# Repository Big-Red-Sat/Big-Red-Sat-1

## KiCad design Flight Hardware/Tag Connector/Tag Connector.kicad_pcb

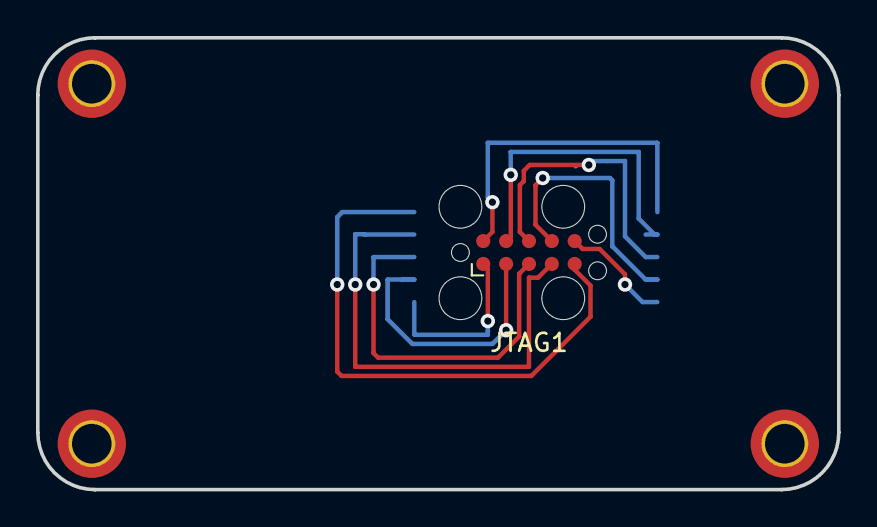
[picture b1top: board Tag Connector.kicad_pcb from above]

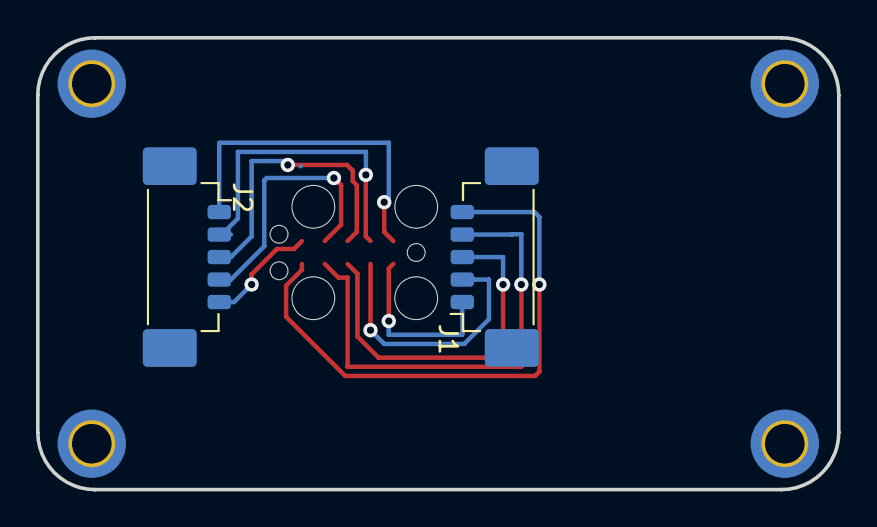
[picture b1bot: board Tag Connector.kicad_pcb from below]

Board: 2 copper layers, 44.5 x 25.1 mm, 3 parts (2 on the bottom side), 10 nets.

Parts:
J1, J2: Conn_01x05_Male; Molex_PicoBlade_53398-0571_1x05-1MP_P1.25mm_Vertical
JTAG1: Conn_02x05_Odd_Even; Tag-Connect_TC2050-IDC-FP_2x05_P1.27mm_Vertical

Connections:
+3V3: J1.1, JTAG1.1
GND: J2.5, JTAG1.6
unnamed: J2.1, JTAG1.10
unnamed: J2.2, JTAG1.9
unnamed: J2.3, JTAG1.8
Rx: J1.5, JTAG1.5
TCK: J1.4, JTAG1.4
TDO-TDI: J1.2, JTAG1.2
TESTVPP: J1.3, JTAG1.3
Tx: J2.4, JTAG1.7

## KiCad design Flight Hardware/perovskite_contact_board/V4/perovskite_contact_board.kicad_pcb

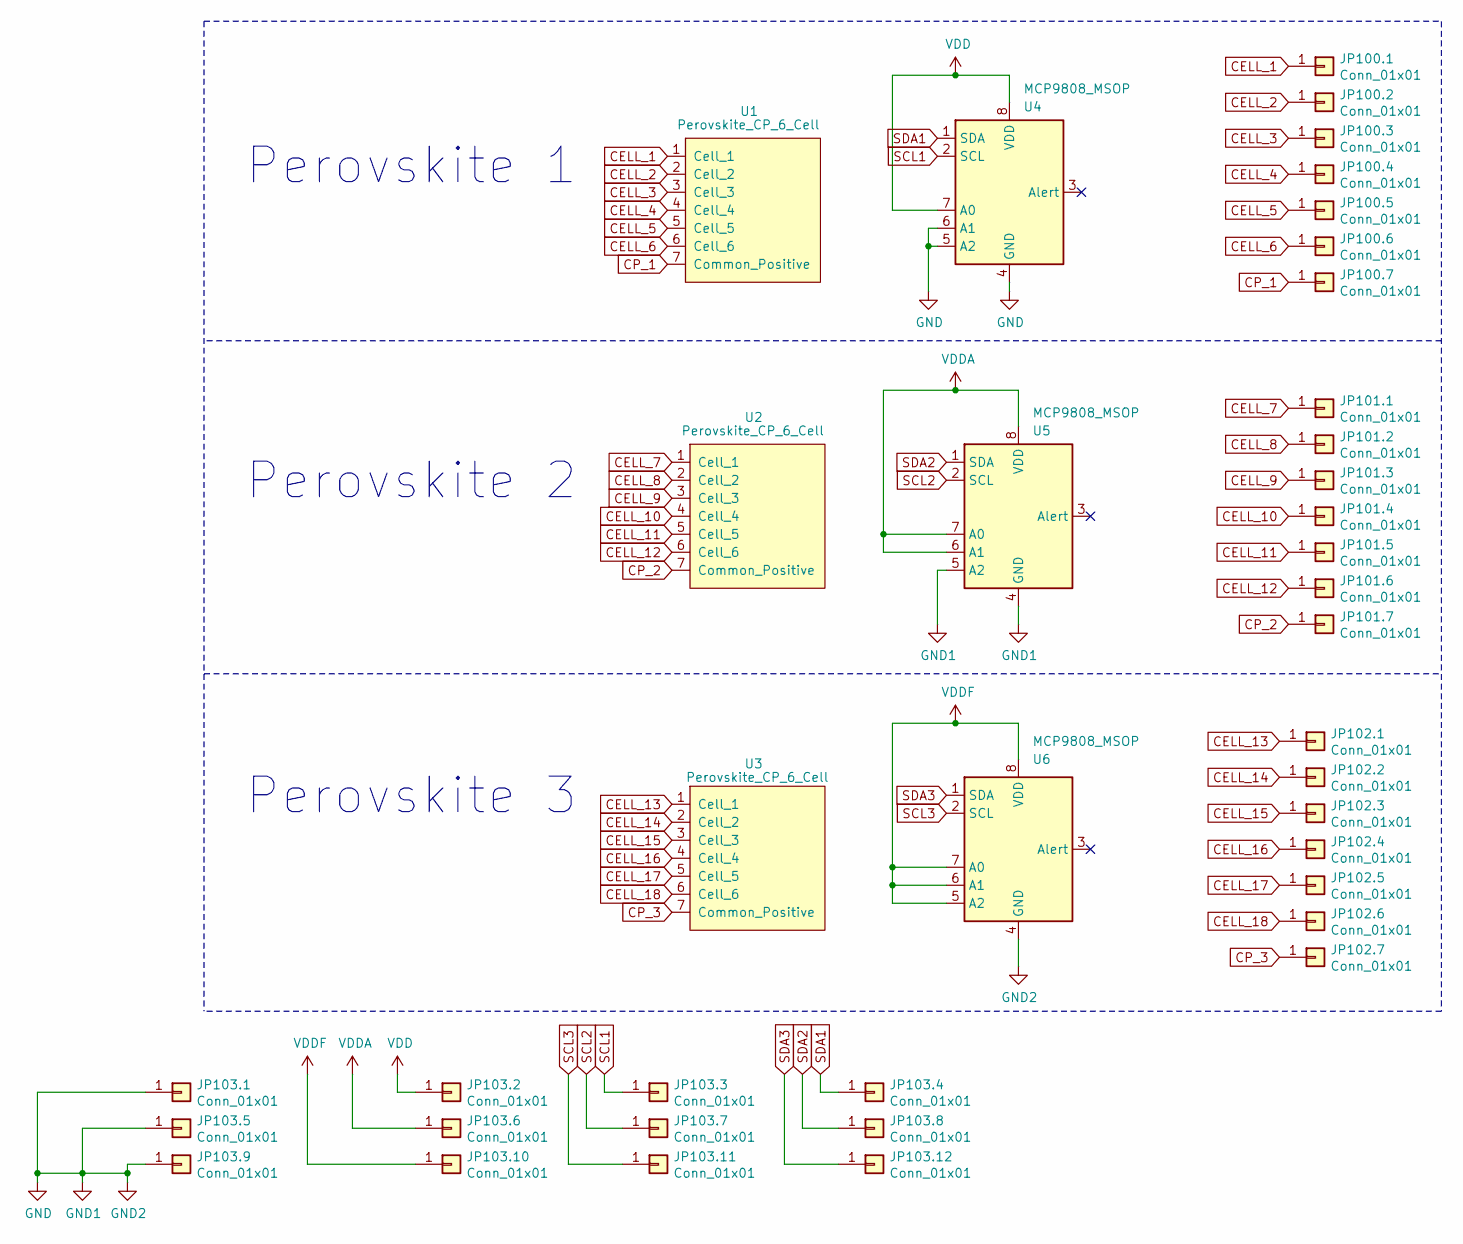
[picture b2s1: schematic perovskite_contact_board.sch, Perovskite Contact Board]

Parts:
JP100.1, JP100.2, JP100.3, JP100.4, JP100.5, JP100.6, JP100.7, JP101.1, JP101.2, JP101.3, JP101.4, JP101.5, JP101.6, JP101.7, JP102.1, JP102.2, JP102.3, JP102.4, JP102.5, JP102.6, JP102.7, JP103.1, JP103.2, JP103.3, JP103.4, JP103.5, JP103.6, JP103.7, JP103.8, JP103.9, JP103.10, JP103.11, JP103.12: Conn_01x01; TestPoint_Pad_D2.0mm
U1, U2, U3: Perovskite_CP_6_Cell; Perovskite
U4, U5, U6: MCP9808_MSOP; MCP9804_With_Hole

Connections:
CELL_1: JP100.1.1, U1.1 (Cell_1)
CELL_2: JP100.2.1, U1.2 (Cell_2)
CELL_3: JP100.3.1, U1.3 (Cell_3)
CELL_4: JP100.4.1, U1.4 (Cell_4)
CELL_5: JP100.5.1, U1.5 (Cell_5)
CELL_6: JP100.6.1, U1.6 (Cell_6)
CELL_7: JP101.1.1, U2.1 (Cell_1)
CELL_8: JP101.2.1, U2.2 (Cell_2)
CELL_9: JP101.3.1, U2.3 (Cell_3)
CELL_10: JP101.4.1, U2.4 (Cell_4)
CELL_11: JP101.5.1, U2.5 (Cell_5)
CELL_12: JP101.6.1, U2.6 (Cell_6)
CELL_13: JP102.1.1, U3.1 (Cell_1)
CELL_14: JP102.2.1, U3.2 (Cell_2)
CELL_15: JP102.3.1, U3.3 (Cell_3)
CELL_16: JP102.4.1, U3.4 (Cell_4)
CELL_17: JP102.5.1, U3.5 (Cell_5)
CELL_18: JP102.6.1, U3.6 (Cell_6)
CP_1: JP100.7.1, U1.7 (Common_Positive)
CP_2: JP101.7.1, U2.7 (Common_Positive)
CP_3: JP102.7.1, U3.7 (Common_Positive)
GND: JP103.1.1, JP103.5.1, JP103.9.1, U4.4 (GND), U4.5 (A2), U4.6 (A1), U5.4 (GND), U5.5 (A2), U6.4 (GND); also elsewhere on the board
SCL1: JP103.3.1, U4.2 (SCL)
SCL2: JP103.7.1, U5.2 (SCL)
SCL3: JP103.11.1, U6.2 (SCL); also elsewhere on the board
SDA1: JP103.4.1, U4.1 (SDA)
SDA2: JP103.8.1, U5.1 (SDA); also elsewhere on the board
SDA3: JP103.12.1, U6.1 (SDA)
VDD: JP103.2.1, U4.7 (A0), U4.8 (VDD); also elsewhere on the board
VDDA: JP103.6.1, U5.6 (A1), U5.7 (A0), U5.8 (VDD); also elsewhere on the board
VDDF: JP103.10.1, U6.5 (A2), U6.6 (A1), U6.7 (A0), U6.8 (VDD); also elsewhere on the board

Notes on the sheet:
Perovskite 1
Perovskite 2
Perovskite 3

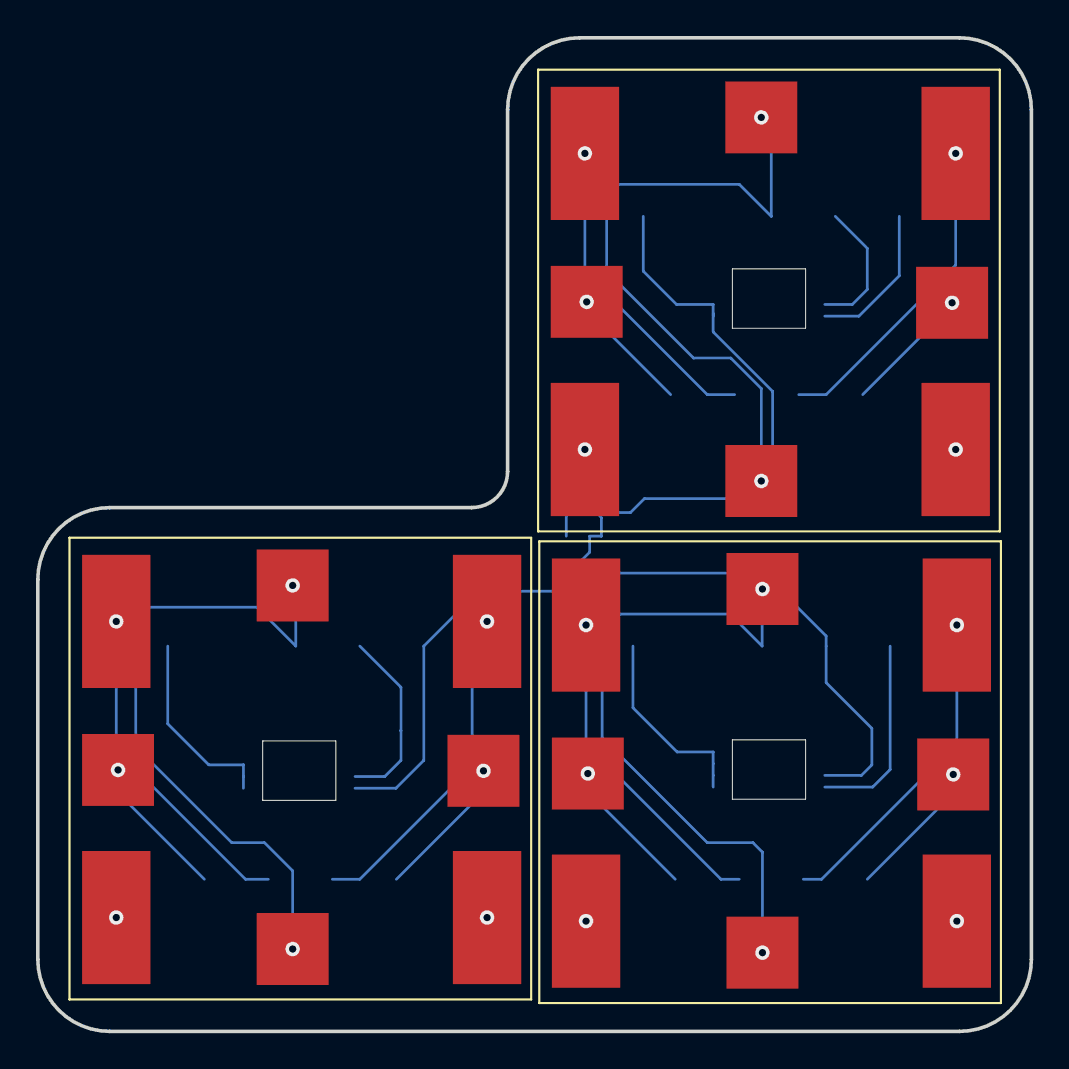
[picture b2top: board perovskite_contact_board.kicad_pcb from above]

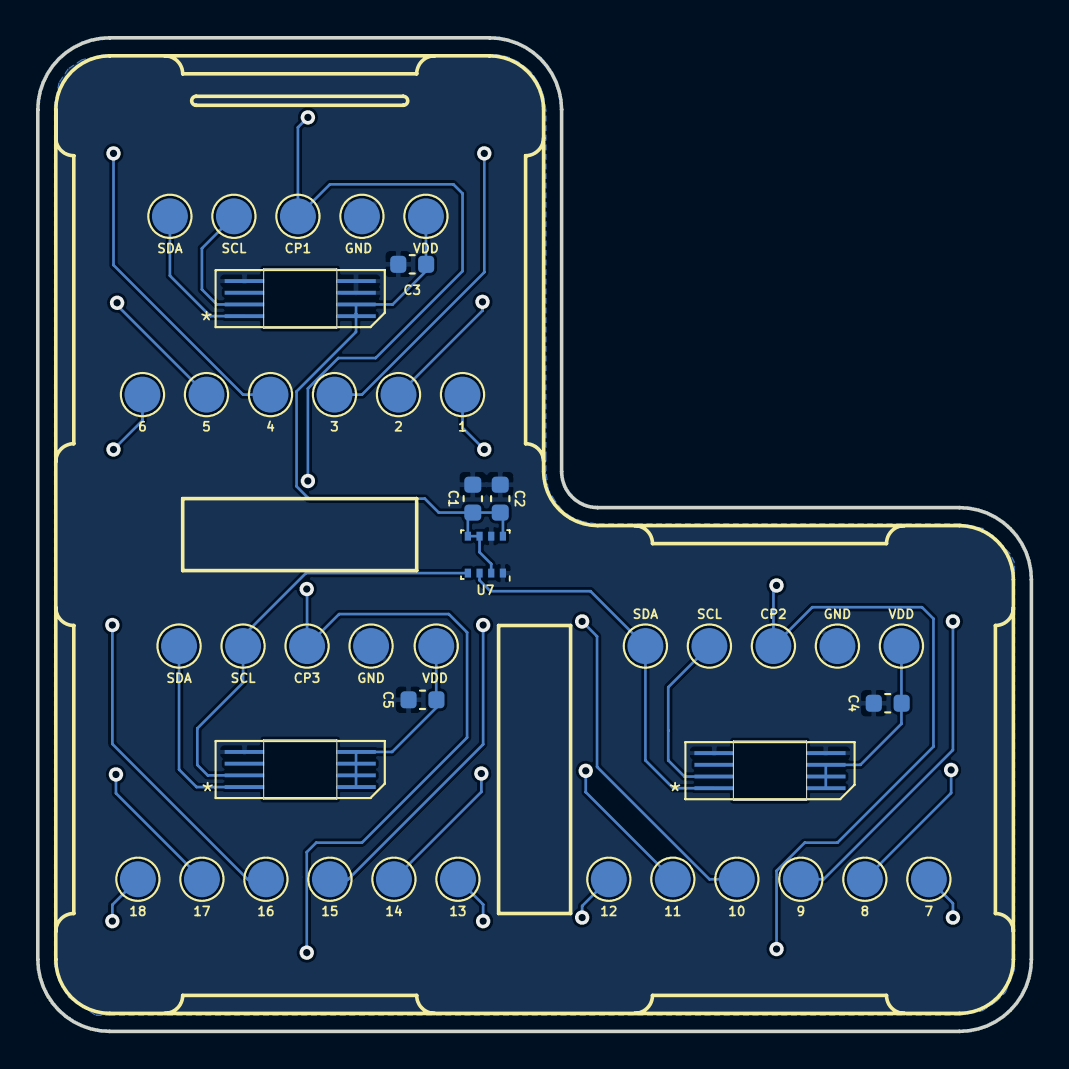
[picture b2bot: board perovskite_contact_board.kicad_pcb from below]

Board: 2 copper layers, 55.2 x 55.2 mm, 45 parts (42 on the bottom side), 31 nets.

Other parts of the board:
C1, C2, C3, C4, C5: 0.1u; C_0603_1608Metric
U7: BME280; Bosch_LGA-8_2.5x2.5mm_P0.65mm_ClockwisePinNumbering

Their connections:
GND: C1.2, C2.2, C3.2, C4.2, C5.2, U7.1, U7.7; also elsewhere on the board
SCL3: U7.4; also elsewhere on the board
SDA2: U7.3; also elsewhere on the board
VDD: C1.1, C2.1, C3.1, U7.2, U7.5, U7.6, U7.8; also elsewhere on the board
VDDA: C4.1; also elsewhere on the board
VDDF: C5.1; also elsewhere on the board

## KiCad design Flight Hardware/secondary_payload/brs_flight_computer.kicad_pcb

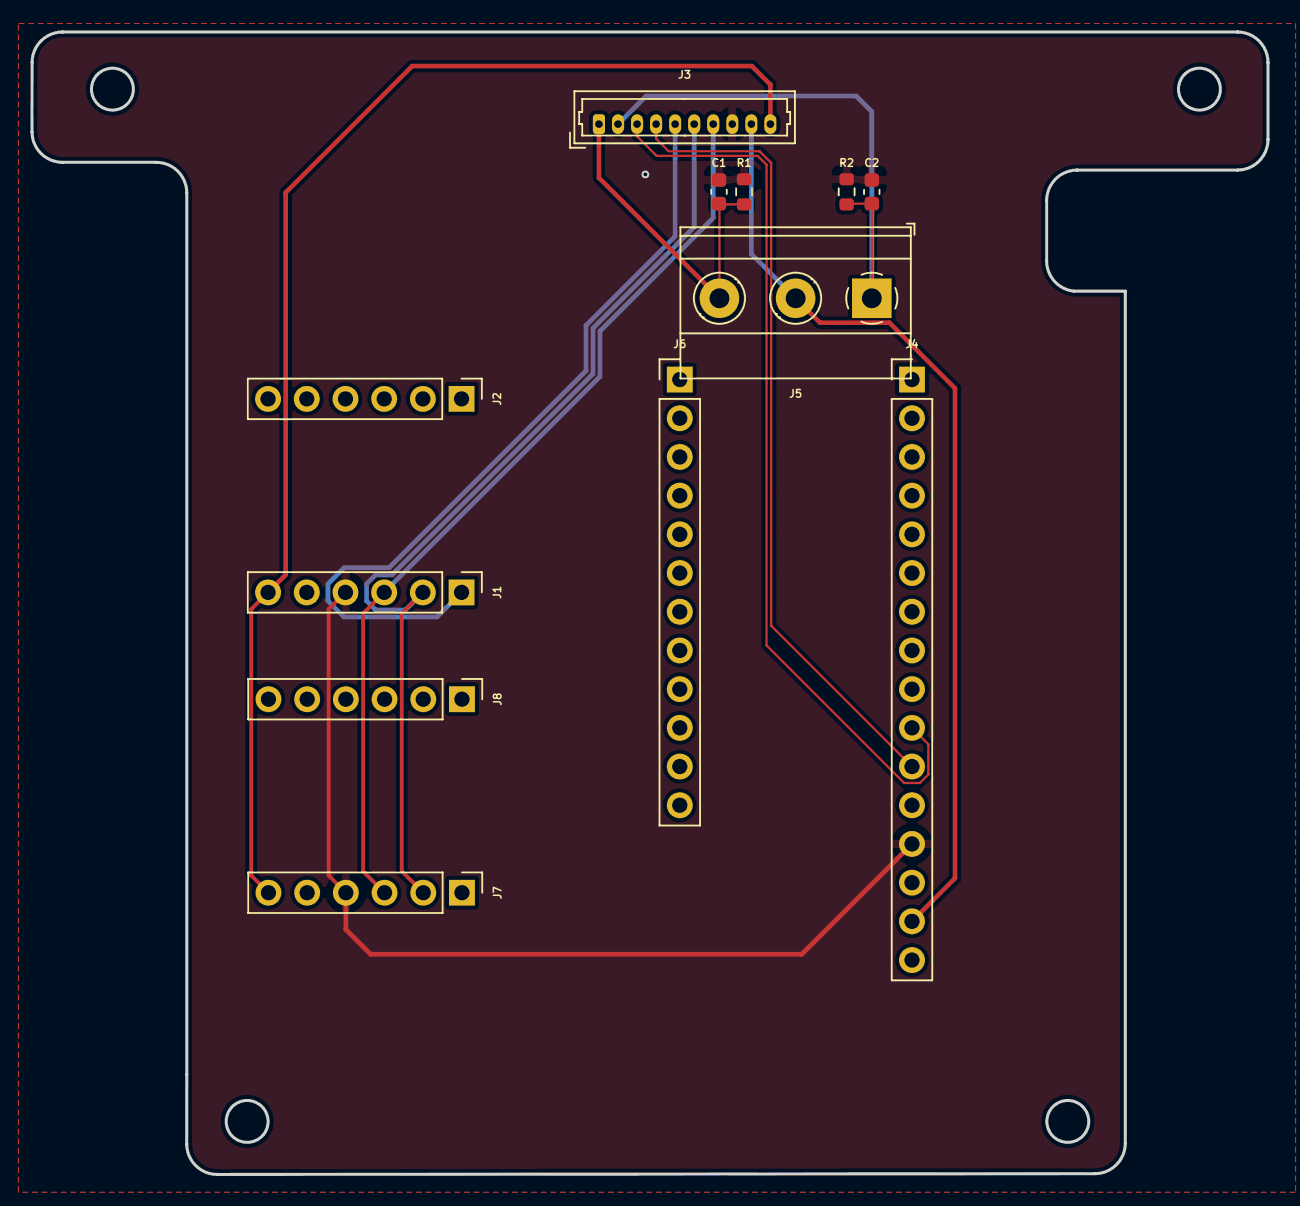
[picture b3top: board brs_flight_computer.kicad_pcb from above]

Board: 2 copper layers, 81.1 x 75.0 mm, 12 parts (0 on the bottom side), 10 nets.

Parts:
C1, C2: C; C_0603_1608Metric
J1, J2, J7, J8: Conn_01x06_Male; PinHeader_1x06_P2.54mm_Vertical
J3: Conn_01x10_Male; Molex_PicoBlade_53047-1010_1x10_P1.25mm_Vertical
J4: Conn_01x16_Male; PinHeader_1x16_P2.54mm_Vertical
J5: Conn_01x03_Male; TerminalBlock_Phoenix_MKDS-1,5-3_1x03_P5.00mm_Horizontal
J6: Conn_01x12_Male; PinHeader_1x12_P2.54mm_Vertical
R1, R2: R; R_0603_1608Metric

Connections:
/MAG_INT: J1.1, J3.5
/NC_V: C1.1, J3.1, J5.3, R1.1
/NO_V: C2.1, J3.2, J5.1, R2.1
/SCL: J1.3, J3.7, J7.3
/SDA: J1.2, J3.6, J7.2
/SET: J3.4, J4.11
/UNSET: J3.3, J4.10
GND: C1.2, C2.2, J1.4, J3.8, J4.13, J7.4, R1.2, R2.2
VDDF: J1.6, J3.10, J7.6
VPP: J3.9, J4.15, J5.2

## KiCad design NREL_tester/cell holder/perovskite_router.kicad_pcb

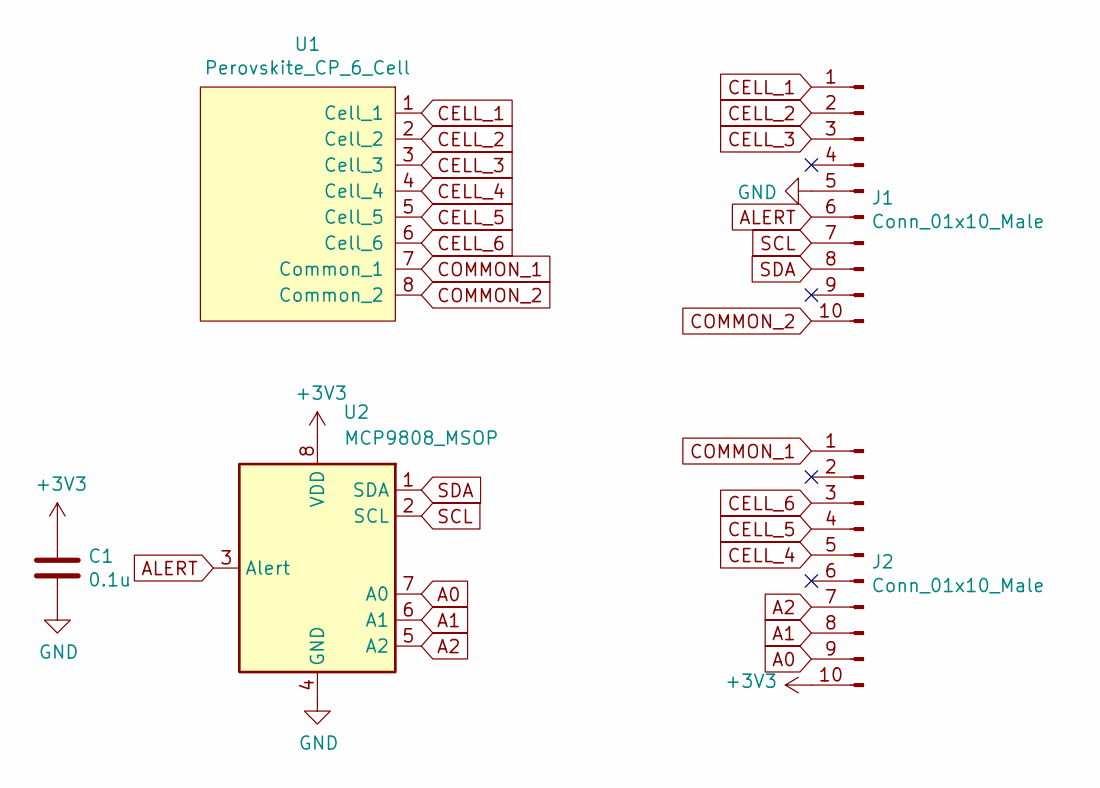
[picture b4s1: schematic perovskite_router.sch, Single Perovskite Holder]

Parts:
C1: 0.1u; C_0603_1608Metric_Pad1.08x0.95mm_HandSolder
J1, J2: Conn_01x10_Male; PinHeader_1x10_P2.54mm_Vertical
U1: Perovskite_CP_6_Cell; Perovskite
U2: MCP9808_MSOP; MCP9804_With_Hole

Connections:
+3V3: C1.1, J2.10, U2.8 (VDD)
A0: J2.9, U2.7 (A0)
A1: J2.8, U2.6 (A1)
A2: J2.7, U2.5 (A2)
ALERT: J1.6, U2.3 (Alert)
CELL_1: J1.1, U1.1 (Cell_1)
CELL_2: J1.2, U1.2 (Cell_2)
CELL_3: J1.3, U1.3 (Cell_3)
CELL_4: J2.5, U1.4 (Cell_4)
CELL_5: J2.4, U1.5 (Cell_5)
CELL_6: J2.3, U1.6 (Cell_6)
COMMON_1: J2.1, U1.7 (Common_1)
COMMON_2: J1.10, U1.8 (Common_2)
GND: C1.2, J1.5, U2.4 (GND)
SCL: J1.7, U2.2 (SCL)
SDA: J1.8, U2.1 (SDA)

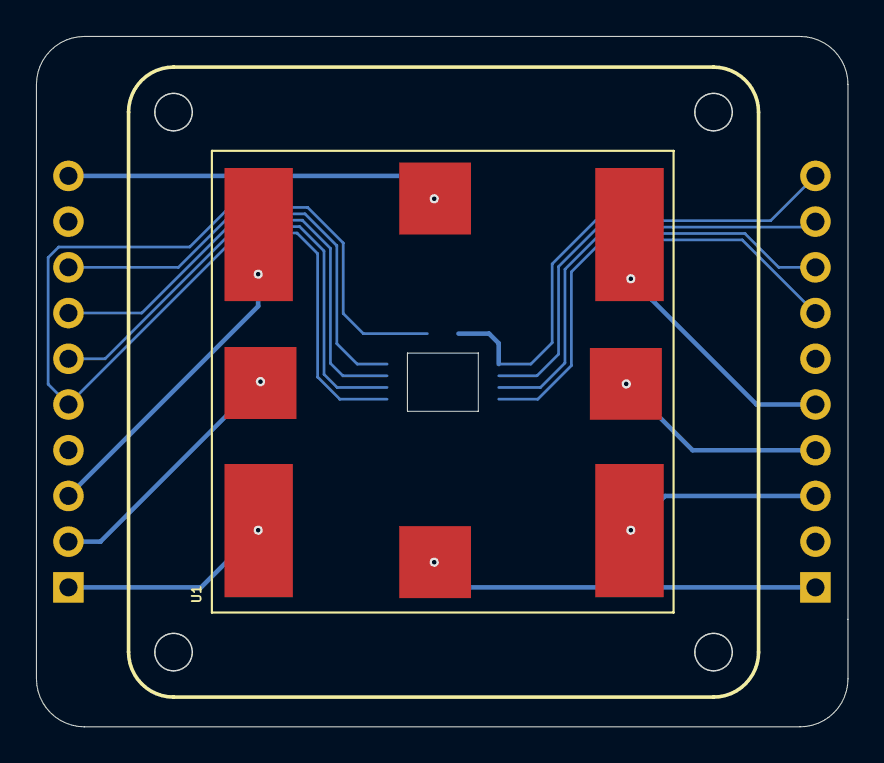
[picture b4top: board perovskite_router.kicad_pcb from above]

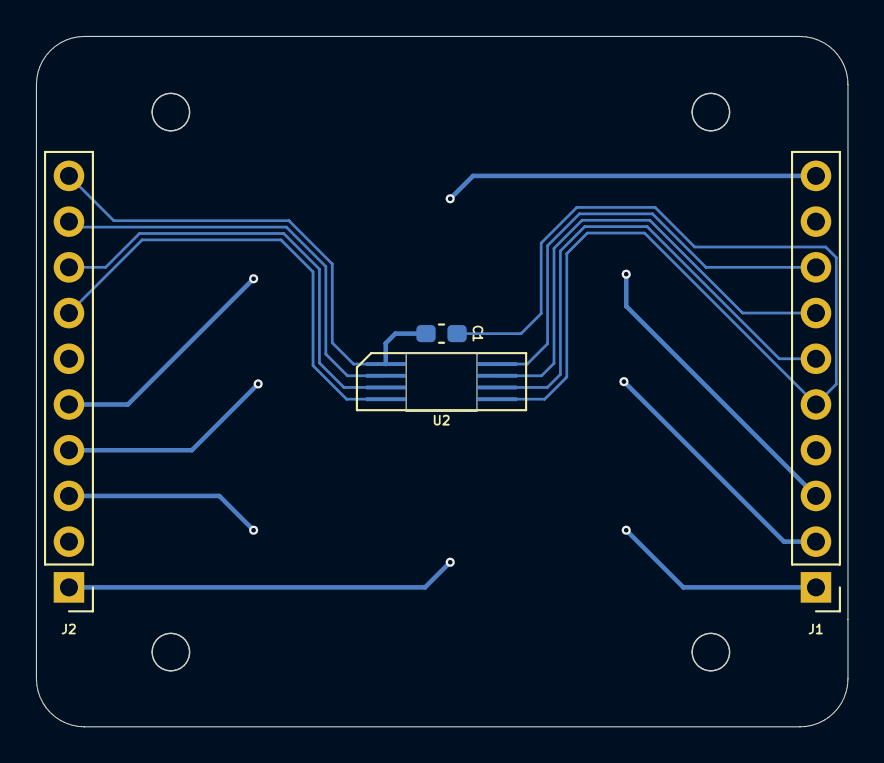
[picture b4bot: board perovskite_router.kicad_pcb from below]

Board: 2 copper layers, 45.1 x 38.4 mm, 5 parts (4 on the bottom side), 16 nets.

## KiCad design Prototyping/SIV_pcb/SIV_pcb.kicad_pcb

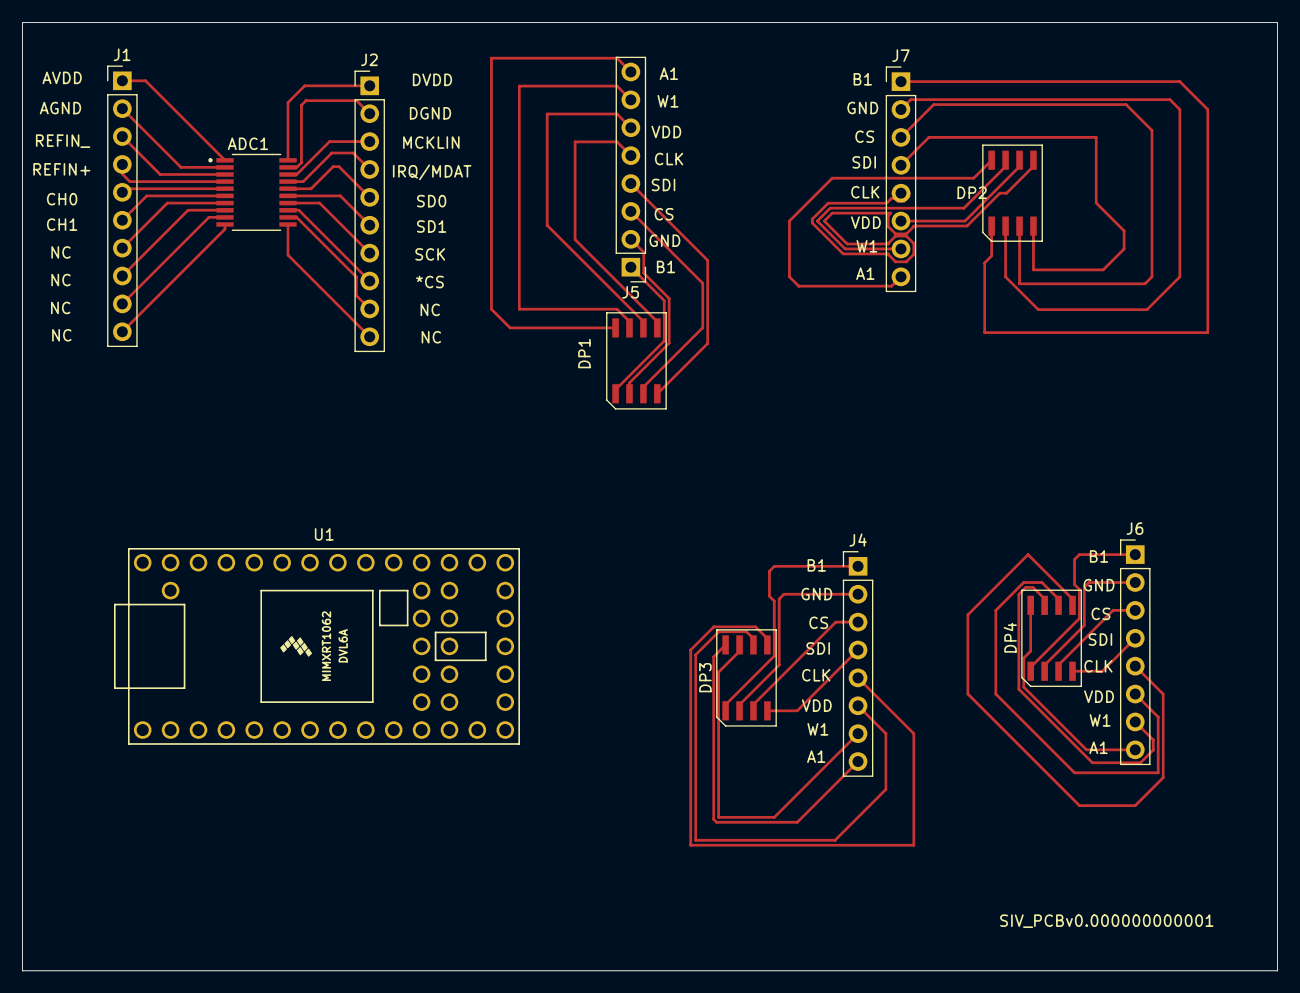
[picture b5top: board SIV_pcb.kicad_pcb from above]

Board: 2 copper layers, 114.3 x 86.4 mm, 12 parts (0 on the bottom side), 52 nets.

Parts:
ADC1: ADC_3461; ADC_MCP3461
DP1, DP2, DP3, DP4: AD8400_DP; AD8400 DP
J1, J2: Conn_01x10_Female; PinHeader_1x10_P2.54mm_Vertical
J4, J5, J6, J7: Conn_01x08_Female; PinHeader_1x08_P2.54mm_Vertical
U1: Teensy4.0; Teensy4_0

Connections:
unnamed: ADC1.11 (NC), J2.10
unnamed: ADC1.12 (NC), J2.9
unnamed: ADC1.13 (*CS), J2.8
unnamed: ADC1.14 (SCK), J2.7
unnamed: ADC1.15 (SD1), J2.6
unnamed: ADC1.16 (SD0), J2.5
unnamed: ADC1.17 (*IRQ/MDAT), J2.4
unnamed: ADC1.18 (MCLKIN), J2.3
unnamed: ADC1.19 (DGND), J2.2
unnamed: ADC1.20 (DVDD), J2.1
unnamed: DP1.1 (B1), J5.1
unnamed: DP1.2 (GND), J5.2
unnamed: DP1.3 (CS), J5.3
unnamed: DP1.4 (SDI), J5.4
unnamed: DP1.5 (A1), J5.5
unnamed: DP1.6 (W1), J5.6
unnamed: DP1.7 (VDD), J5.7
unnamed: DP1.8 (CLK), J5.8
unnamed: DP2.1 (B1), J7.1
unnamed: DP2.2 (GND), J7.2
unnamed: DP2.3 (CS), J7.3
unnamed: DP2.4 (SDI), J7.4
unnamed: DP2.5 (A1), J7.5
unnamed: DP2.6 (W1), J7.6
unnamed: DP2.7 (VDD), J7.7
unnamed: DP2.8 (CLK), J7.8
unnamed: DP3.1 (B1), J4.1
unnamed: DP3.2 (GND), J4.2
unnamed: DP3.3 (CS), J4.3
unnamed: DP3.4 (SDI), J4.4
unnamed: DP3.5 (A1), J4.5
unnamed: DP3.6 (W1), J4.6
unnamed: DP3.7 (VDD), J4.7
unnamed: DP3.8 (CLK), J4.8
unnamed: DP4.1 (B1), J6.1
unnamed: DP4.2 (GND), J6.2
unnamed: DP4.3 (CS), J6.3
unnamed: DP4.4 (SDI), J6.4
unnamed: DP4.6 (W1), J6.6
unnamed: DP4.7 (VDD), J6.7
unnamed: DP4.8 (CLK), J6.8
unnamed: ADC1.1 (AVDD), J1.1
unnamed: ADC1.2 (AGND), J1.2
unnamed: ADC1.3 (REFIN_), J1.3
unnamed: ADC1.4 (REFIN+), J1.4
unnamed: ADC1.5 (CH0), J1.5
unnamed: ADC1.6 (CH1), J1.6
unnamed: ADC1.7 (NC), J1.7
unnamed: ADC1.8 (NC), J1.8
unnamed: ADC1.9 (NC), J1.9
unnamed: ADC1.10 (NC), J1.10
unnamed: DP4.5 (A1), J6.5

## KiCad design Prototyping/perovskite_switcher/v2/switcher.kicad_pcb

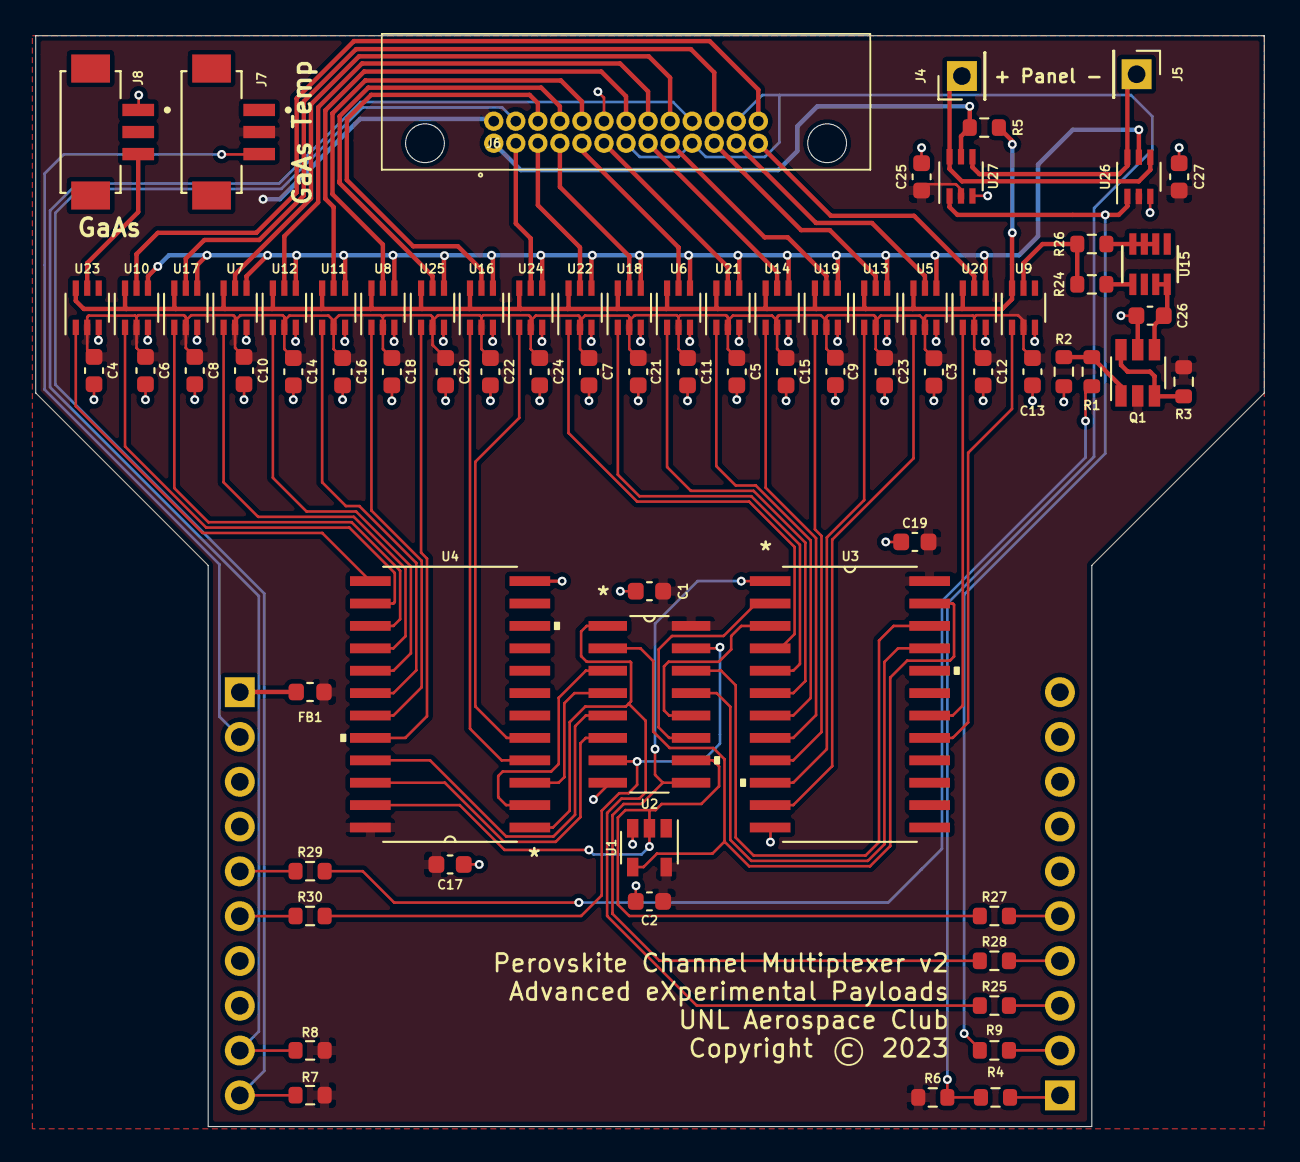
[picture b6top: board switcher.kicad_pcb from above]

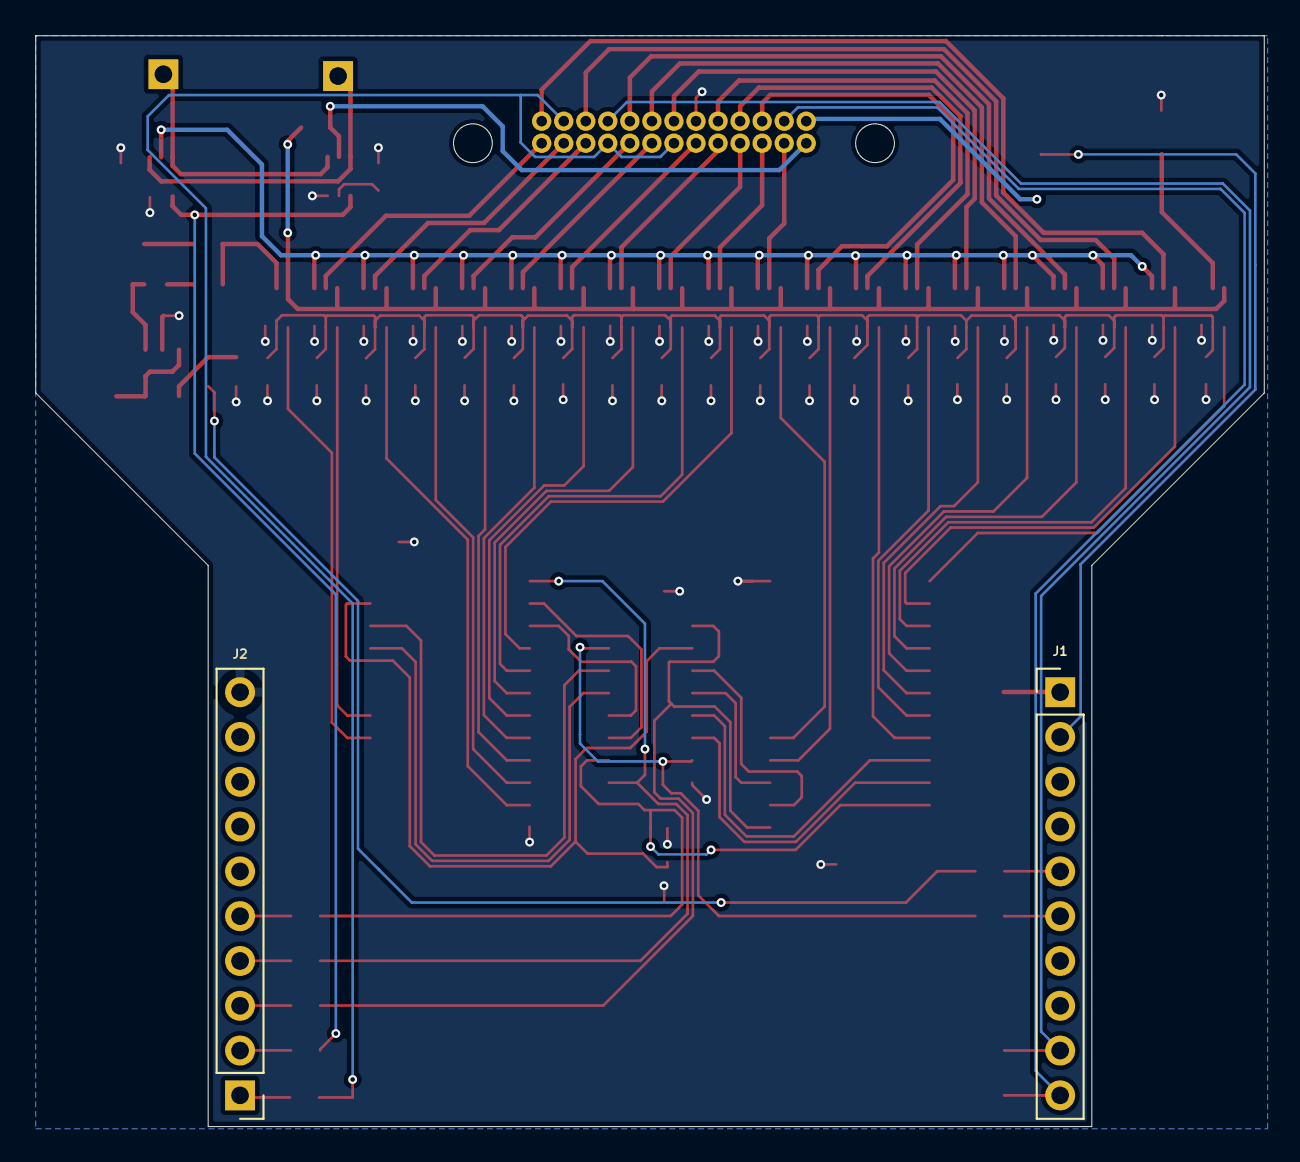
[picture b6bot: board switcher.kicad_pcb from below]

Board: 2 copper layers, 69.7 x 61.8 mm, 79 parts (2 on the bottom side), 79 nets.

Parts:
C1, C2, C3, C4, C5, C6, C7, C8, C9, C10, C11, C12, C13, C14, C15, C16, C17, C18, C19, C20, C21, C22, C23, C24, C25, C26, C27: 0.1u; C_0603_1608Metric
FB1: Ferrite_Bead; L_0603_1608Metric
J1, J2: Conn_01x10_Female; PinHeader_1x10_P2.54mm_Vertical
J4: Positive Output to Curve Tracer; PinHeader_1x01_P2.54mm_Vertical
J5: Negative Output to Curve Tracer; PinHeader_1x01_P2.54mm_Vertical
J6: G125-MH12605M4R
J7, J8: DF13C-3P-1.25V(21); HRS_DF13C-3P-1.25V(21)
Q1: DMC2053UVT; TSOT-23-6
R1: 1k; R_0603_1608Metric
R2, R3: 10k; R_0603_1608Metric
R4, R5, R6, R7, R8, R9, R25, R27, R28, R29, R30: 100; R_0603_1608Metric
R24: 20k; R_0603_1608Metric
R26: 1; R_0603_1608Metric
U1: SN74LVC1G14DRL; SOT-23-5
U2: CD4518BM96
U3, U4: CD4514BM
U5, U6, U7, U8, U9, U10, U11, U12, U13, U14, U16, U17, U18, U19, U20, U21, U22, U23, U24, U25, U26, U27: ADG839YKSZ-REEL7
U15: LT3092ETS8TRPBF; TSOT-23_TS8

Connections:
0-9_CLOCK: R25.1, U2.1, U4.1
10-19_CLOCK: R28.1, U2.9, U3.1
+3V3: C1.1, C2.1, C3.1, C4.1, C5.1, C6.1, C7.1, C8.1, C9.1, C10.1, C11.1, C12.1, C13.1, C14.1, C15.1, C16.1, C17.1, C18.1, C19.1, C20.1, C21.1, C22.1, C23.1, C24.1, C25.1, C27.1, FB1.1, J6.14, J7.2, Q1.2, R3.1, R6.2, R7.2, R8.2, U1.5, U2.16, U3.24, U4.24, U5.2, U6.2, U7.2, U8.2, U9.2, U10.2, U11.2, U12.2, U13.2, U14.2, U16.2, U17.2, U18.2, U19.2, U20.2, U21.2, U22.2, U23.2, U24.2, U25.2, U26.2, U27.2
ENABLE_PANEL_SWITCH: R27.1, U1.2, U2.10, U4.23
ENABLE_TEST_SOURCE: R1.2, R29.1
GND: C1.2, C2.2, C3.2, C4.2, C5.2, C6.2, C7.2, C8.2, C9.2, C10.2, C11.2, C12.2, C13.2, C14.2, C15.2, C16.2, C17.2, C18.2, C19.2, C20.2, C21.2, C22.2, C23.2, C24.2, C25.2, C26.1, C27.2, J2.10, J6.19, J8.1, Q1.5, R2.2, U1.3, U2.8, U3.12, U4.12, U5.3, U6.3, U7.3, U8.3, U9.3, U10.3, U11.3, U12.3, U13.3, U14.3, U16.3, U17.3, U18.3, U19.3, U20.3, U21.3, U22.3, U23.3, U24.3, U25.3, U26.3, U27.3
unnamed: C26.2, Q1.4, U15.7, U15.8
unnamed: FB1.2, J1.1
unnamed: J1.2, J7.3
unnamed: J1.5, R29.2
unnamed: J1.6, R30.1
unnamed: J2.1, R4.2
unnamed: J2.2, R9.2
unnamed: J2.3, R25.2
unnamed: J2.4, R28.2
unnamed: J2.5, R27.2
unnamed: J4.1, U26.4, U27.6
unnamed: J5.1, U26.6, U27.4
unnamed: J6.1, R5.1, U27.5
unnamed: J6.2, U24.5
unnamed: J6.3, U22.5
unnamed: J6.4, U18.5
unnamed: J6.5, U6.5
unnamed: J6.6, U21.5
unnamed: J6.8, U14.5
unnamed: J6.9, U19.5
unnamed: J6.11, U13.5
unnamed: J6.12, U5.5
unnamed: J6.13, U20.5
unnamed: J6.16, U16.5
unnamed: J6.17, U25.5
unnamed: J6.18, U8.5
unnamed: J6.20, U11.5
unnamed: J6.21, U12.5
unnamed: J6.22, U7.5
unnamed: J6.24, U17.5
unnamed: J6.26, U10.5
unnamed: J8.3, U23.5
unnamed: Q1.1, R1.1, R2.1
unnamed: Q1.3, Q1.6, R3.2
unnamed: R5.2, U5.6, U6.6, U7.6, U8.6, U9.6, U10.6, U11.6, U12.6, U13.6, U14.6, U16.6, U17.6, U18.6, U19.6, U20.6, U21.6, U22.6, U23.6, U24.6, U25.6
unnamed: R24.2, U15.5
unnamed: R26.2, U15.2, U15.3, U15.4
unnamed: U2.3, U4.2
unnamed: U2.4, U4.3
unnamed: U2.5, U4.21
unnamed: U2.6, U4.22
unnamed: U2.11, U3.2
unnamed: U2.12, U3.3
unnamed: U2.13, U3.21
unnamed: U2.14, U3.22
unnamed: U3.6, U6.1
unnamed: U3.11, U5.1
unnamed: U3.17, U9.1
unnamed: U4.16, U7.1
unnamed: U4.19, U8.1
unnamed: U4.14, U10.1
unnamed: U5.4, U6.4, U7.4, U8.4, U10.4, U11.4, U12.4, U13.4, U14.4, U16.4, U17.4, U18.4, U19.4, U20.4, U21.4, U22.4, U24.4, U25.4, U26.5
unnamed: U4.18, U11.1
unnamed: U4.17, U12.1
unnamed: U3.10, U13.1
unnamed: U3.8, U14.1
unnamed: U4.4, U16.1
unnamed: U4.15, U17.1
unnamed: U3.5, U18.1
unnamed: U3.9, U19.1
unnamed: U3.18, U20.1
unnamed: U3.7, U21.1
unnamed: U3.4, U22.1
unnamed: U4.13, U23.1
unnamed: U4.5, U24.1
unnamed: U4.20, U25.1
RESET_PANEL_SWITCH: R30.2, U2.7, U2.15
REVERSE_BIAS: R9.1, U26.1, U27.1
SCL: J1.9, J6.23, R8.1
SDA: J1.10, J6.15, R7.1
TEST_SOURCE: R24.1, R26.1, U9.5
~ALERT: J6.7, J6.10, J6.25, R4.1, R6.1
~ENABLE_PANEL_SWITCH: U1.4, U2.2, U3.23

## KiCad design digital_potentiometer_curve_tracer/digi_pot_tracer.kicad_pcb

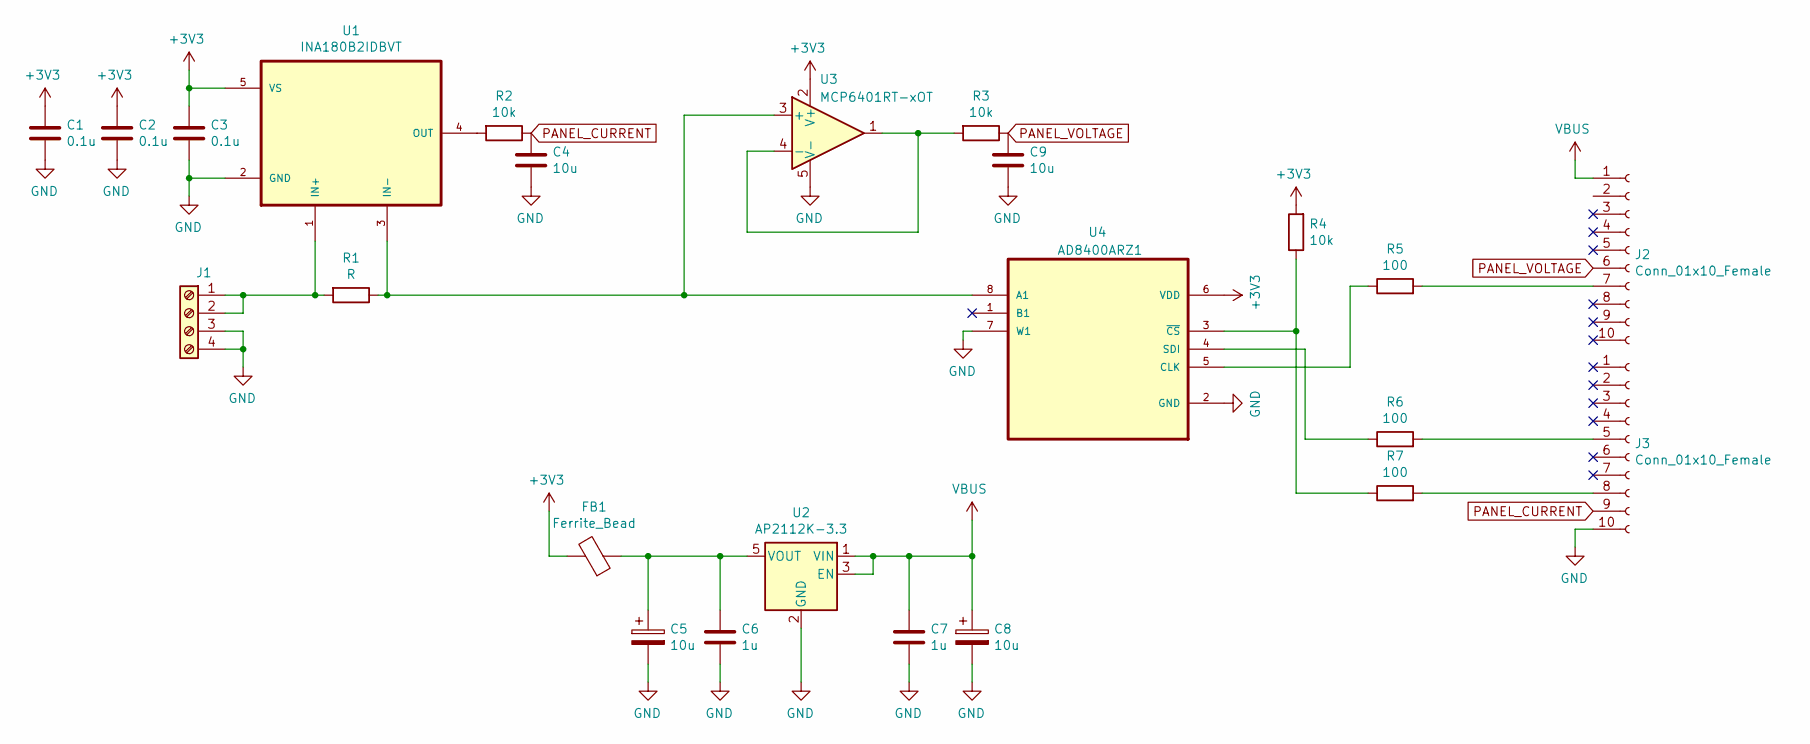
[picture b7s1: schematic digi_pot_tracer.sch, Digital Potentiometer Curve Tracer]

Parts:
C1, C2, C3: 0.1u; C_0603_1608Metric
C4, C9: 10u; C_0603_1608Metric
C5, C8: 10u; C_1206_3216Metric
C6, C7: 1u; C_0603_1608Metric
FB1: Ferrite_Bead; L_0603_1608Metric
J1: Screw_Terminal_01x04; TerminalBlock_Phoenix_MKDS-3-4-5.08_1x04_P5.08mm_Horizontal
J2, J3: Conn_01x10_Female; PinHeader_1x10_P2.54mm_Vertical
R1: R; R_1206_3216Metric
R2, R3, R4: 10k; R_0603_1608Metric
R5, R6, R7: 100; R_0603_1608Metric
U1: INA180B2IDBVT; SOT95P280X145-5N
U2: AP2112K-3.3; SOT-23-5
U3: MCP6401RT-xOT; SOT-23-5
U4: AD8400ARZ1; SOIC127P600X175-8N; MPN AD8400ARZ1

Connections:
+3V3: C1.1, C2.1, C3.1, FB1.2, R4.2, U1.5 (VS), U3.2 (V+), U4.6 (VDD)
GND: C1.2, C2.2, C3.2, C4.2, C5.2, C6.2, C7.2, C8.2, C9.2, J1.3, J1.4, J3.10, U1.2 (GND), U2.2 (GND), U3.5 (V-), U4.2 (GND), U4.7 (W1)
unnamed: C5.1, C6.1, FB1.1, U2.5 (VOUT)
unnamed: J1.1, J1.2, R1.2, U1.1 (IN+)
unnamed: J2.7, R5.2
unnamed: J3.5, R6.2
unnamed: J3.8, R7.2
unnamed: R1.1, U1.3 (IN-), U3.3 (+), U4.8 (A1)
unnamed: R2.2, U1.4 (OUT)
unnamed: R3.2, U3.1, U3.4 (-)
unnamed: R4.1, R7.1, U4.3 (~CS)
unnamed: R5.1, U4.5 (CLK)
unnamed: R6.1, U4.4 (SDI)
PANEL_CURRENT: C4.1, J3.9, R2.1
PANEL_VOLTAGE: C9.1, J2.6, R3.1
VBUS: C7.1, C8.1, J2.1, U2.1 (VIN), U2.3 (EN)

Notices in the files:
Flight Hardware/perovskite_contact_board/V3/perovskite_contact_board.sch:
Copyright (c) 2023
Prototyping/perovskite_switcher/v2/switcher.kicad_pcb:
Copyright (c) 2022
parts and their libraries:
Copyright 2021 Accelerated Designs. All rights reserved.
